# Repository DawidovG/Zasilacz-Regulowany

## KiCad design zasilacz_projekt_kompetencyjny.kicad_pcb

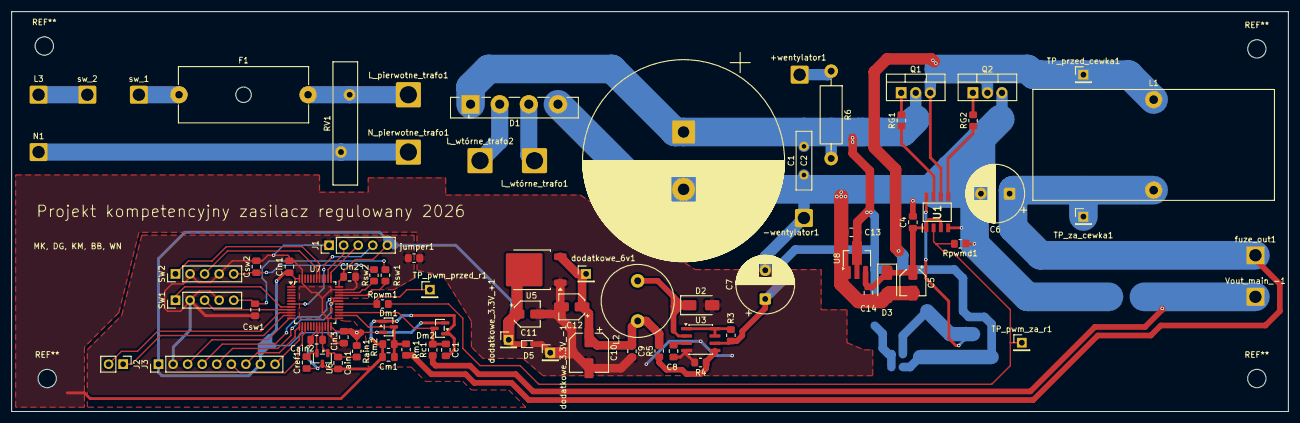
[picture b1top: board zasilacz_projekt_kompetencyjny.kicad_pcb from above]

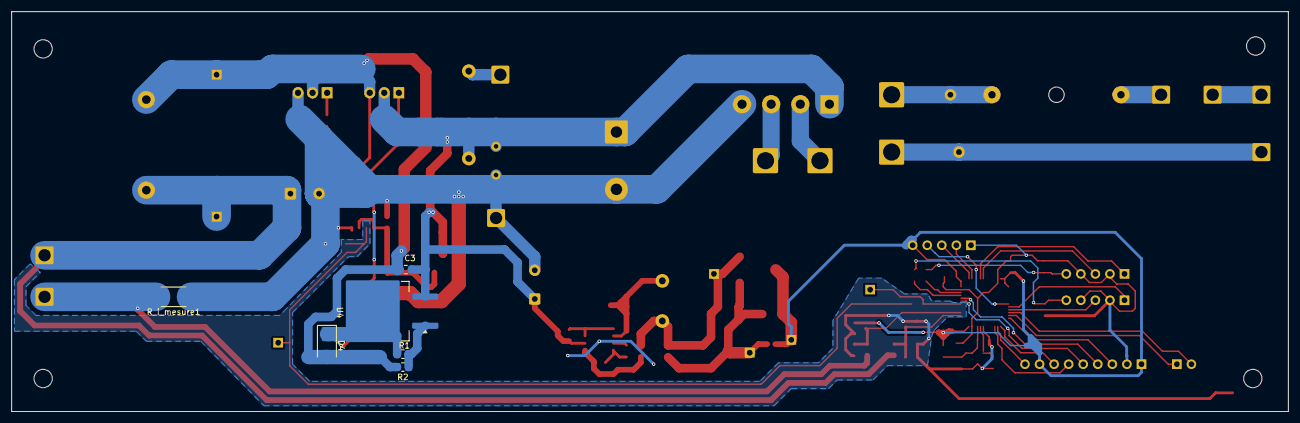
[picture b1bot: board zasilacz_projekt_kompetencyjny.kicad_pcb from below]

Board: 2 copper layers, 222.7 x 69.8 mm, 86 parts (6 on the bottom side), 51 nets.

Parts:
+wentylator1: Conn_01x01_Pin; SolderWire-1.5sqmm_1x01_D1.7mm_OD3mm
-wentylator1: Conn_01x01_Pin; SolderWire-1.5sqmm_1x01_D1.7mm_OD3mm
C1: 6800u; CP_Radial_D35.0mm_P10.00mm_SnapIn
C2: 100n; C_Disc_D10.0mm_W2.5mm_P5.00mm
C3, C4, C9: 100n; C_0805_2012Metric_Pad1.18x1.45mm_HandSolder
C5: 4.7uF; CP_Elec_4x5.8
C6: 330uF; CP_Radial_D10.0mm_P5.00mm
C7: 100u; CP_Radial_D10.0mm_P5.00mm
C8: 220p; C_0805_2012Metric_Pad1.18x1.45mm_HandSolder
C10: 180u; CP_Elec_6.3x7.7
C11, C12: 10u; CP_Elec_4x5.8
C13, C14: 10u; C_0805_2012Metric_Pad1.18x1.45mm_HandSolder
Cain1: >1uF; C_0805_2012Metric_Pad1.18x1.45mm_HandSolder
Cain2: 100n; C_0805_2012Metric_Pad1.18x1.45mm_HandSolder
Cc1: 10n; C_0805_2012Metric_Pad1.18x1.45mm_HandSolder
Cin1, Cin2, Cin3: 100n; C_0805_2012Metric_Pad1.18x1.45mm_HandSolder
Cm1: 100n; C_0805_2012Metric_Pad1.18x1.45mm_HandSolder
Cref1: 10uF; C_0805_2012Metric_Pad1.18x1.45mm_HandSolder
Csw1, Csw2: 100n; C_0805_2012Metric_Pad1.18x1.45mm_HandSolder
D1: GBU8B; Diode_Bridge_Vishay_GBU
D2: SS36; D_SMA
D3, D4: SMAJ12A; D_SMA
D5: ESD5Zxx; D_SOD-523
Dm1, Dm2: BAT54S; SOT-23
F1: Fuse; Fuseholder_Cylinder-5x20mm_Schurter_0031_8201_Horizontal_Op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
J1: Program Connector; PinHeader_1x05_P2.54mm_Vertical
J2: UART; PinHeader_1x02_P2.54mm_Vertical
J3: LCD ILI9488; PinHeader_1x09_P2.54mm_Vertical
L1: 100uH; L_Toroid_Vertical_L41.9mm_W19.1mm_P15.80mm_Vishay_TJ7
L2: 100u; L_Radial_D12.5mm_P7.00mm_Fastron_09HCP
L3: Conn_01x01_Pin; SolderWire-1.5sqmm_1x01_D1.7mm_OD3mm
L_pierwotne_trafo1: Conn_01x01_Pin; SolderWire-2.5sqmm_1x01_D2.4mm_OD4.4mm
L_wtórne_trafo1, L_wtórne_trafo2: Conn_01x01_Pin; SolderWire-2.5sqmm_1x01_D2.4mm_OD4.4mm
N1: Conn_01x01_Pin; SolderWire-1.5sqmm_1x01_D1.7mm_OD3mm
N_pierwotne_trafo1: Conn_01x01_Pin; SolderWire-2.5sqmm_1x01_D2.4mm_OD4.4mm
Q1, Q2: FQP30N06L; TO-220-3_Vertical
R1, R4: 1k; R_0805_2012Metric_Pad1.20x1.40mm_HandSolder
R2: 7.33k; R_0805_2012Metric_Pad1.20x1.40mm_HandSolder
R3: 0.33; R_0805_2012Metric_Pad1.20x1.40mm_HandSolder
R5: 3.8k; R_0805_2012Metric_Pad1.20x1.40mm_HandSolder
R6: 200; R_Axial_DIN0411_L9.9mm_D3.6mm_P15.24mm_Horizontal
RG1, RG2: 10; R_0805_2012Metric_Pad1.20x1.40mm_HandSolder
RV1: Varistor; RV_Disc_D21.5mm_W4.3mm_P10mm
R_i_mesure1: 0.1; R_2512_6332Metric_Pad1.40x3.35mm_HandSolder
Rain1: 10; R_0805_2012Metric_Pad1.20x1.40mm_HandSolder
Rc1: 1k; R_0805_2012Metric_Pad1.20x1.40mm_HandSolder
Rm1: 27k; R_0805_2012Metric_Pad1.20x1.40mm_HandSolder
Rm2: 3k; R_0805_2012Metric_Pad1.20x1.40mm_HandSolder
Rpwm1: 22; R_0805_2012Metric_Pad1.20x1.40mm_HandSolder
Rpwmd1: 10k; R_0805_2012Metric_Pad1.20x1.40mm_HandSolder
Rsw1, Rsw2: 10k; R_0805_2012Metric_Pad1.20x1.40mm_HandSolder
SW1: Voltage; PinHeader_1x05_P2.54mm_Vertical
SW2: Current; PinHeader_1x05_P2.54mm_Vertical
TP_przed_cewka1: Conn_01x01_Pin; PinHeader_1x01_P2.54mm_Vertical
TP_pwm_przed_r1: Conn_01x01_Pin; PinHeader_1x01_P2.54mm_Vertical
TP_pwm_za_r1: Conn_01x01_Pin; PinHeader_1x01_P2.54mm_Vertical
TP_za_cewka1: Conn_01x01_Pin; PinHeader_1x01_P2.54mm_Vertical
U1: IR2109; SOIC127P600X175-8N
U3: MC34063AD; SOIC-8_3.9x4.9mm_P1.27mm
U4: LM317_TO-263; TO-263-2
U5: NCP1117-3.3_SOT223; TO-252-2
U6: REF3030; SOT-23
U7: STM32G431CBTx; LQFP-48_7x7mm_P0.5mm
U8: LDI75L12UA; SOT-89-3_Handsoldering
Vout_main_-1: Conn_01x01_Pin; SolderWire-1.5sqmm_1x01_D1.7mm_OD3mm
dodatkowe_3.3V_+1, dodatkowe_3.3V_-1, dodatkowe_6v1: Conn_01x01_Pin; PinHeader_1x01_P2.54mm_Vertical
fuze_out1: Fuse; SolderWire-1.5sqmm_1x01_D1.7mm_OD3mm
jumper1: 0; R_0805_2012Metric_Pad1.20x1.40mm_HandSolder
sw_1, sw_2: Conn_01x01_Pin; SolderWire-1.5sqmm_1x01_D1.7mm_OD3mm

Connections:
3.3V: C11.1, Cin1.2, Cin2.2, Cin3.2, D5.1 (K), Dm1.2 (K), Dm2.2 (K), J1.5, J3.1, J3.8, Rain1.1, U5.2 (VO), U7.1 (VBAT), U7.24 (VDD), U7.36 (VDD), U7.48 (VDD), dodatkowe_3.3V_+1.1 (Pin_1_1)
/digital/CurrentMeasure: Cc1.1, Dm2.3 (COM), Rc1.2, U7.27 (PB13)
/digital/LCD_SPI1_CS: J3.3, U7.12 (PA4)
/digital/LCD_SPI1_MISO: J3.9, U7.14 (PA6)
/digital/LCD_SPI1_MOSI: J3.6, U7.15 (PA7)
/digital/LCD_SPI1_SCK: J3.7, U7.13 (PA5)
/digital/OutVoltageMeasure: Cm1.1, Dm1.3 (COM), Rm1.2, Rm2.1, U7.26 (PB12)
/digital/PC_UART_RX: J2.1, U7.11 (PA3)
/digital/PC_UART_TX: J2.2, U7.10 (PA2)
/digital/RST: J1.4, U7.7 (PG10)
/digital/SWCLK: J1.2, U7.38 (PA14)
/digital/SWDIO: J1.3, U7.37 (PA13)
/input_power/L: F1.1, sw_1.1 (Pin_1_1)
/input_power/N: N1.1 (Pin_1_1), N_pierwotne_trafo1.1 (Pin_1_1), RV1.2
GND: -wentylator1.1 (Pin_1_1), C1.2, C2.2, C4.2, C5.2, C6.2, C7.2, C8.2, C9.2, C10.2, C11.2, C12.2, C13.2, C14.2, Cain1.2, Cain2.2, Cc1.2, Cm1.2, Cref1.1, D1.4 (-), D2.2 (A), D3.2 (A2), D5.2 (A), Dm1.1 (A), Dm2.1 (A), Q2.3 (S), R4.1, R_i_mesure1.1, Rm2.2, Rpwmd1.1, U1.4 (COM), U3.4 (GND), U5.1 (GND), U6.3 (GND), U7.19 (VSSA), U8.1 (GND), dodatkowe_3.3V_-1.1 (Pin_1_1), jumper1.2
GNDD: Cin1.1, Cin2.1, Cin3.1, Csw1.1, Csw2.2, J1.1, J3.2, SW1.2 (C_C), SW1.4 (S1_S1), SW2.2 (C_C), SW2.4 (S1_S1), U7.23 (VSS), U7.35 (VSS), U7.47 (VSS), jumper1.1
unnamed: +wentylator1.1 (Pin_1_1), R6.1
unnamed: Csw1.2, Rsw1.2, SW1.5 (S2_S2)
unnamed: Csw2.1, Rsw2.1, SW2.5 (S2_S2)
unnamed: D2.1 (K), L2.1, U3.2 (SwE)
unnamed: C4.1, C5.1, C14.1, D3.1 (A1), U1.1 (VCC), U1.3 (~SD), U8.3 (OUT)
unnamed: D4.1 (A1), R1.1, U1.8 (VB), U4.2 (VO)
unnamed: C3.2, D4.2 (A2), L1.1, Q1.3 (S), Q2.2 (D), R2.2, TP_przed_cewka1.1 (Pin_1_1), U1.6 (VS)
unnamed: J3.4, U7.32 (PA10)
unnamed: J3.5, U7.31 (PA9)
unnamed: L3.1 (Pin_1_1), sw_2.1 (Pin_1_1)
unnamed: F1.2, L_pierwotne_trafo1.1 (Pin_1_1), RV1.1
unnamed: D1.3, L_wtórne_trafo1.1 (Pin_1_1)
unnamed: D1.2, L_wtórne_trafo2.1 (Pin_1_1)
unnamed: Q1.1 (G), RG1.2
unnamed: Q2.1 (G), RG2.2
unnamed: Rpwm1.1, TP_pwm_przed_r1.1 (Pin_1_1), U7.30 (PA8)
unnamed: RG1.1, U1.7 (HO)
unnamed: RG2.1, U1.5 (LO)
unnamed: R3.2, U3.1 (SwC), U3.7 (Ipk), U3.8 (DC)
unnamed: C8.1, U3.3 (TC)
unnamed: R4.2, R5.1, U3.5 (Vfb)
unnamed: R1.2, R2.1, U4.1 (ADJ)
unnamed: C9.1, C10.1, C12.1, L2.2, R5.2, U5.3 (VI), dodatkowe_6v1.1 (Pin_1_1)
unnamed: Cain1.1, Cain2.1, Rain1.2, U6.1 (IN), U7.21 (VDDA)
unnamed: Cref1.2, U6.2 (OUT), U7.20 (VREF+)
unnamed: SW1.1 (A_A), U7.8 (PA0)
unnamed: SW1.3 (B_B), U7.9 (PA1)
unnamed: Rsw1.1, U7.33 (PA11)
unnamed: Rsw2.2, U7.34 (PA12)
unnamed: SW2.1 (A_A), U7.41 (PB4)
unnamed: SW2.3 (B_B), U7.42 (PB5)
OUT_GND_i_mesure: R_i_mesure1.2, Rc1.1, Vout_main_-1.1 (Pin_1_1)
PWM_IN: Rpwm1.2, Rpwmd1.2, TP_pwm_za_r1.1 (Pin_1_1), U1.2 (IN)
Vin_32v: C1.1, C2.1, C3.1, C7.1, C13.1, D1.1 (+), Q1.2 (D), R3.1, R6.2, U3.6 (Vin), U4.3 (VI), U8.2 (IN)
Vinm: C6.1, L1.2, Rm1.1, TP_za_cewka1.1 (Pin_1_1), fuze_out1.1

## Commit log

2026-03-29 Inicjalizacja repozytorium
2026-03-29 input power update
2026-04-09 dodanie zasilania pomocniczego 10v oraz 5v i
2026-04-12 Zmiana nazwy plików i organizacja projektu
2026-04-12 Dodanie części cyfrowej i procesora stm32g4
2026-04-12 Create README.md
    Dodanie readme
2026-04-12 zmiana sekcji zasilania digital oraz drivera
2026-04-14 aktualizacja wartości cewki i kondensatora w przetwornicy głównej
2026-04-19 dodanie testpointów, diody tvs, rezystora pomiarowego
2026-04-25 Dodanie złącza pinowego do wyświetlacza Ili9488 i złącza uart oraz numeracja elementów
2026-04-25 dodanie footprintów w sekcji input power
2026-04-26 dodanie footprintów do main buck (jeszcze driver i razystor bramek) poprawiony pinout LDI75L12UA, dodane footprinty do digital power
2026-04-29 Dodanie brakującego połączenia do przycisków enkoderów
2026-04-29 Przydzielenie brakujących footprintów dla części cyfrowej oprócz enkoderów
2026-04-29 Wstępne dodanie elementów na pcb oraz zmiana numeracji pinów do połączenia enkoderów. Zmiana symboli enkoderów na wersję bez masy i usunięcie zbędnego połączenia masy
2026-04-29 Dodanie obwodów odsprzęgających do przycisków enkoderów
2026-05-04 walidacja schematu, dodanie footprintu do drivera, ERC
2026-05-06 dodanie pcb vin
2026-05-06 Pętla mocy i wyjście zasilania. Sterownik bramek tranzystorów
2026-05-10 dodanie wentylatora, drobne zmiany wartości elementów
2026-05-12 Narysowanie części cyfrowej płytki, części zasialania przetwornicy głównej oraz zasilania części cyfrowej, do dokończenia połączenia mas oraz zasilań
2026-05-13 zakończenie projektu pcb
2026-05-15 Revert "."
    This reverts commit 8e1f65562e8ea6083fc58ea6eeb054cbc5253cd6.
